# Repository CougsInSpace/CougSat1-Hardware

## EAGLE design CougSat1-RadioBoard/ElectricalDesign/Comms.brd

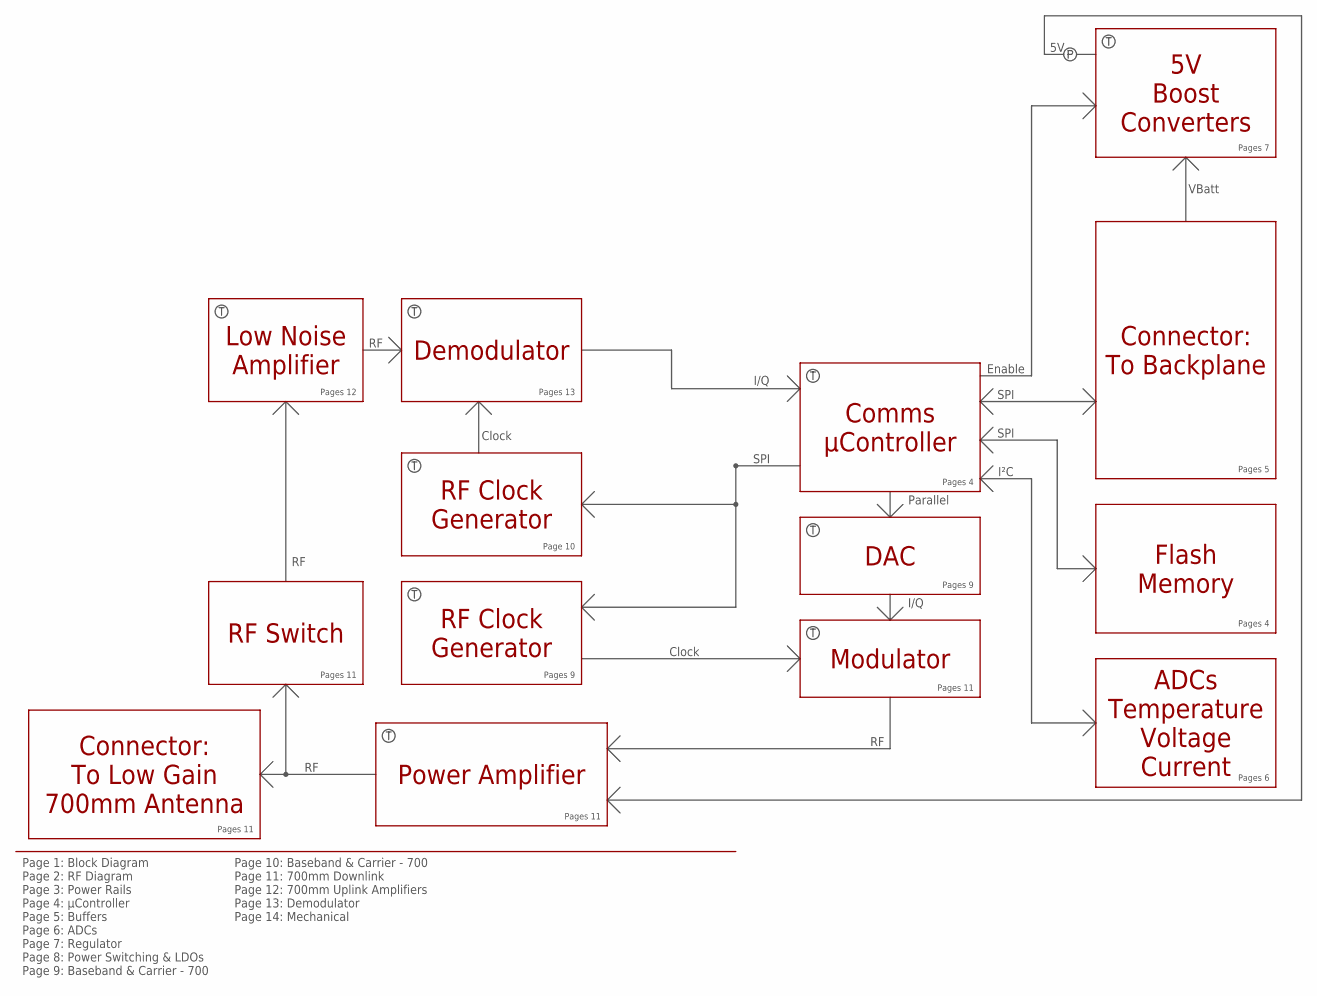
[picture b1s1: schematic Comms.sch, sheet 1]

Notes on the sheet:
Page 1: Block Diagram Page 2: RF Diagram Page 3: Power Rails Page 4: µController Page 5: Buffers Page 6: ADCs Page 7: Regulator Page 8: Power Switching & LDOs Page 9: Baseband & Carrier - 700
Connector: To Backplane
Comms µController
5V Boost Converters
Modulator
RF Clock Generator
Power Amplifier
Connector: To Low Gain 700mm Antenna
RF Switch
Demodulator
Low Noise Amplifier
ADCs Temperature Voltage Current
Flash Memory
VBatt
SPI
I/Q
Clock
Enable
I²C
Page 10: Baseband & Carrier - 700 Page 11: 700mm Downlink Page 12: 700mm Uplink Amplifiers Page 13: Demodulator Page 14: Mechanical
Pages 6
Page 10
DAC
Parallel
Pages 4
Pages 5
Pages 7
Pages 13
Pages 12
Pages 9
Pages 11

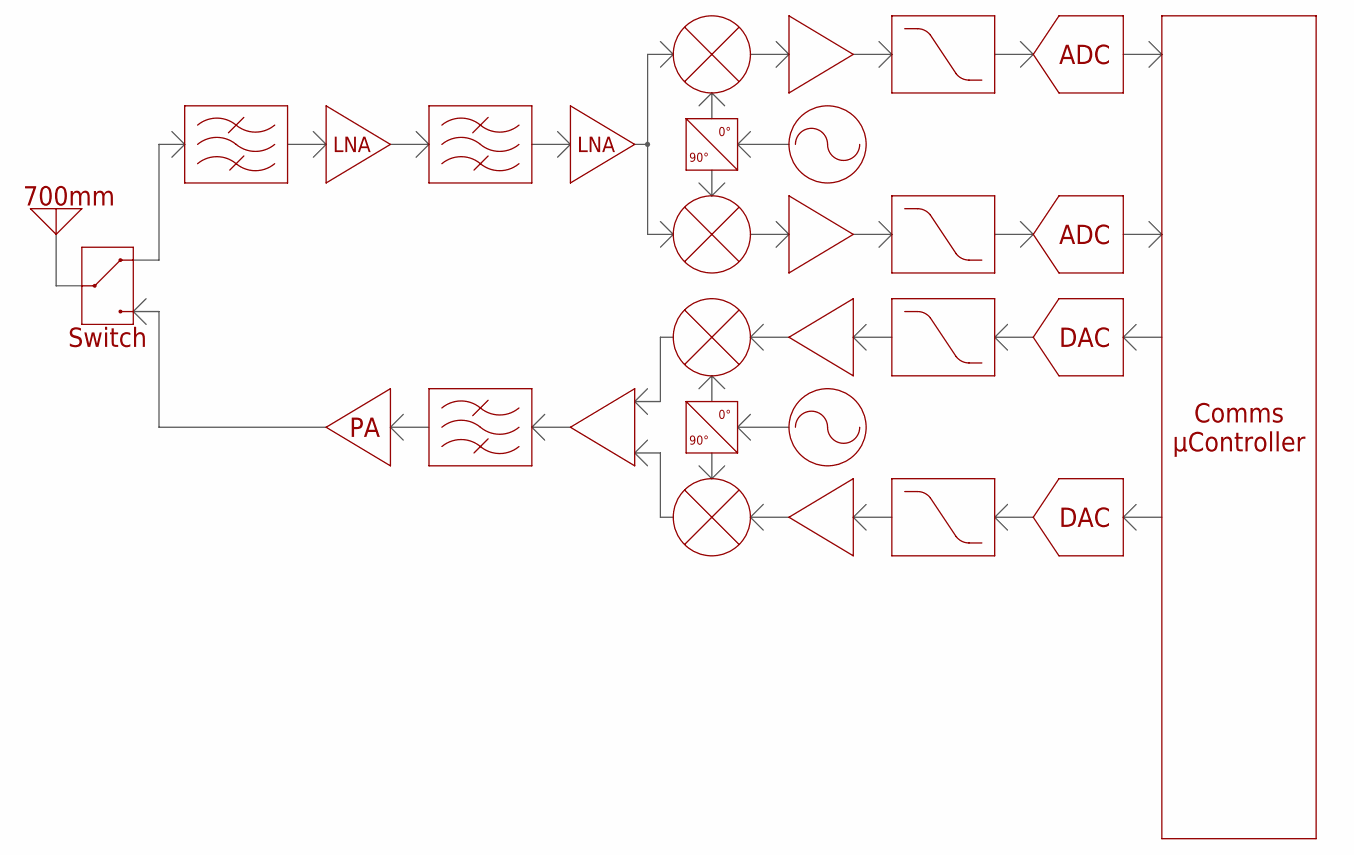
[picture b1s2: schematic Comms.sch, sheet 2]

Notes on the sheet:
LNA
DAC
ADC
90°
Switch
Comms µController
700mm

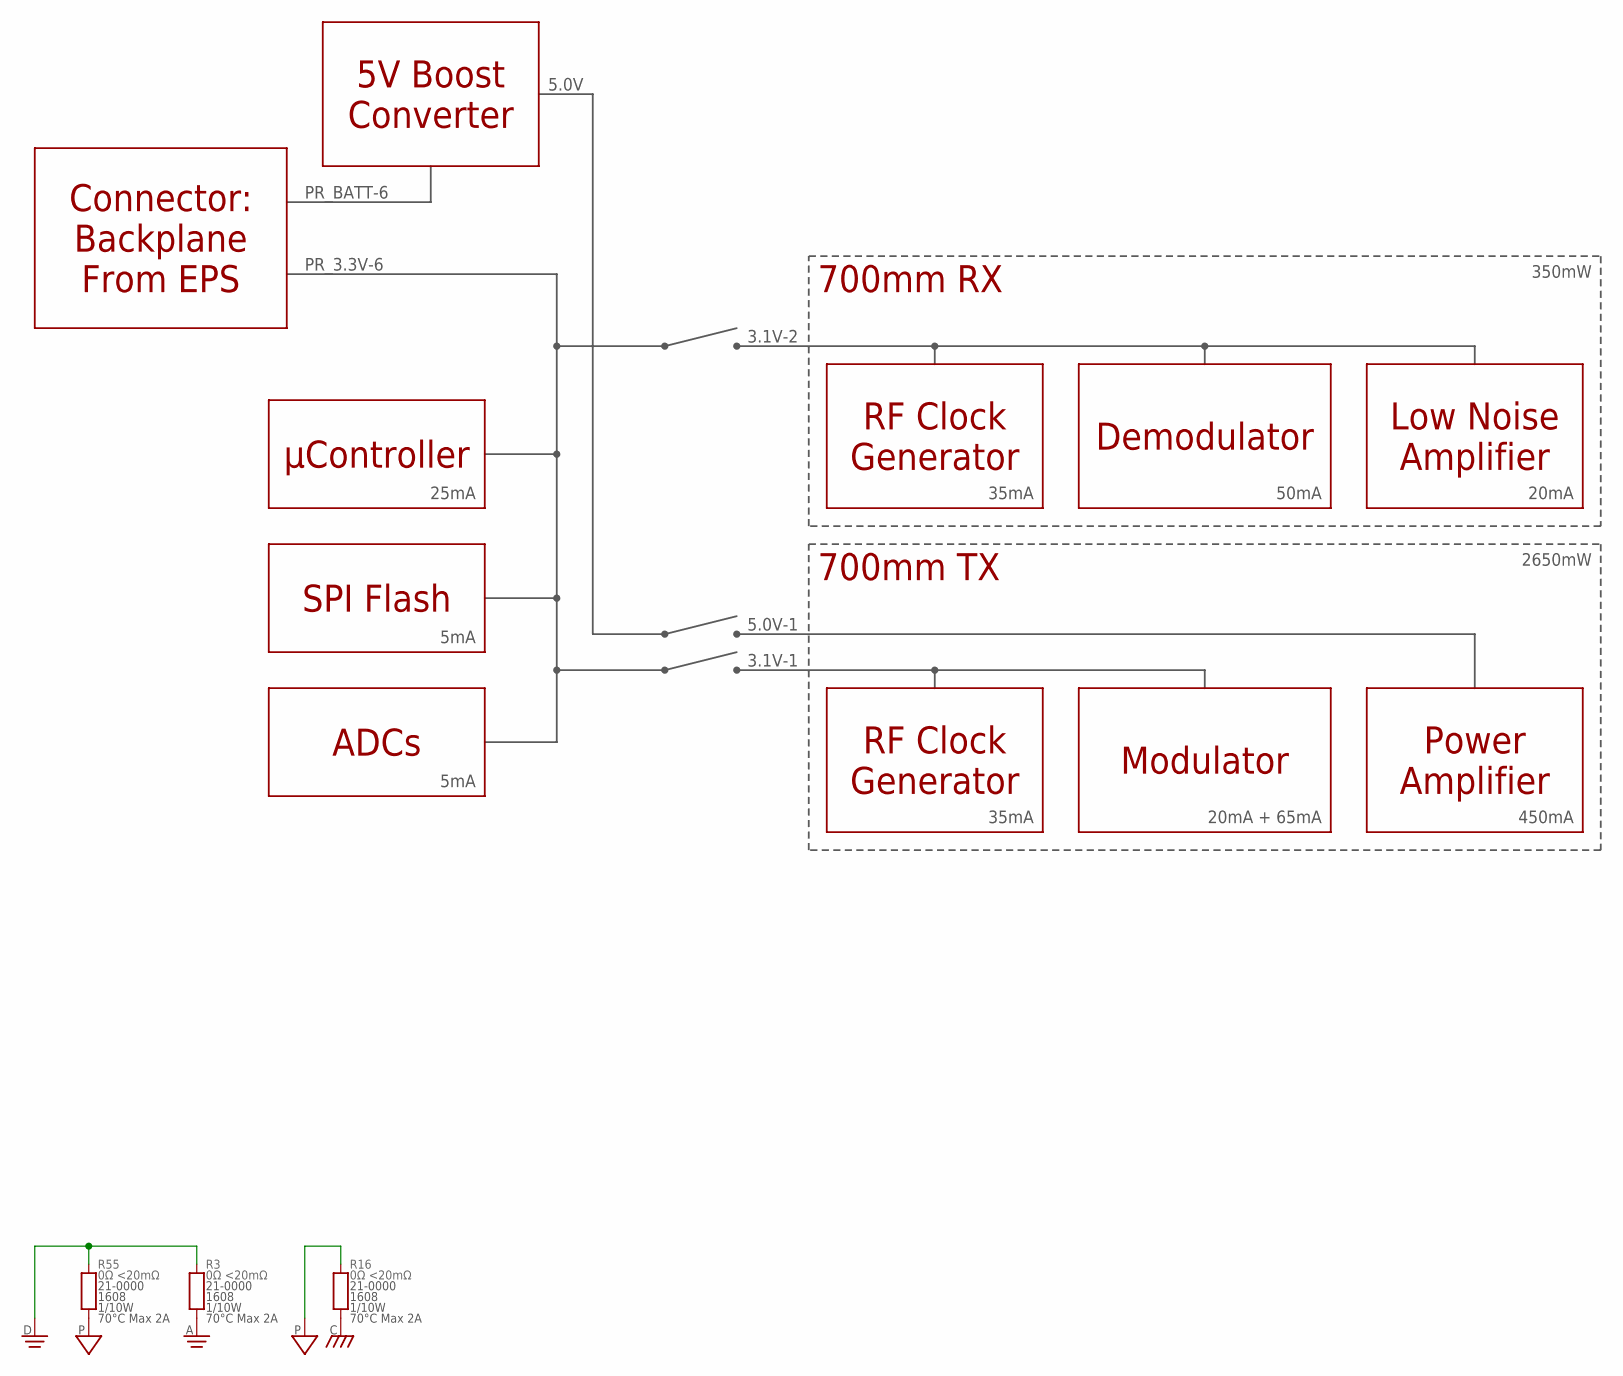
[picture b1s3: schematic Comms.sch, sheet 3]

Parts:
R3, R16, R55: 0Ω <20mΩ; 1608

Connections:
AGND: R3.1; also elsewhere on the board
CHASSIS: R16.1; also elsewhere on the board
DGND: R3.2, R55.2; also elsewhere on the board
PGND: R16.2, R55.1; also elsewhere on the board

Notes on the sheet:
Connector: Backplane From EPS
5V Boost Converter
µController
RF Clock Generator
Low Noise Amplifier
SPI Flash
ADCs
Demodulator
5.0V
PR_BATT-6
Modulator
700mm RX
700mm TX
3.1V-2
3.1V-1
PR_3.3V-6
5.0V-1
Power Amplifier
20mA
20mA + 65mA
50mA
35mA
450mA
25mA
5mA
350mW
2650mW

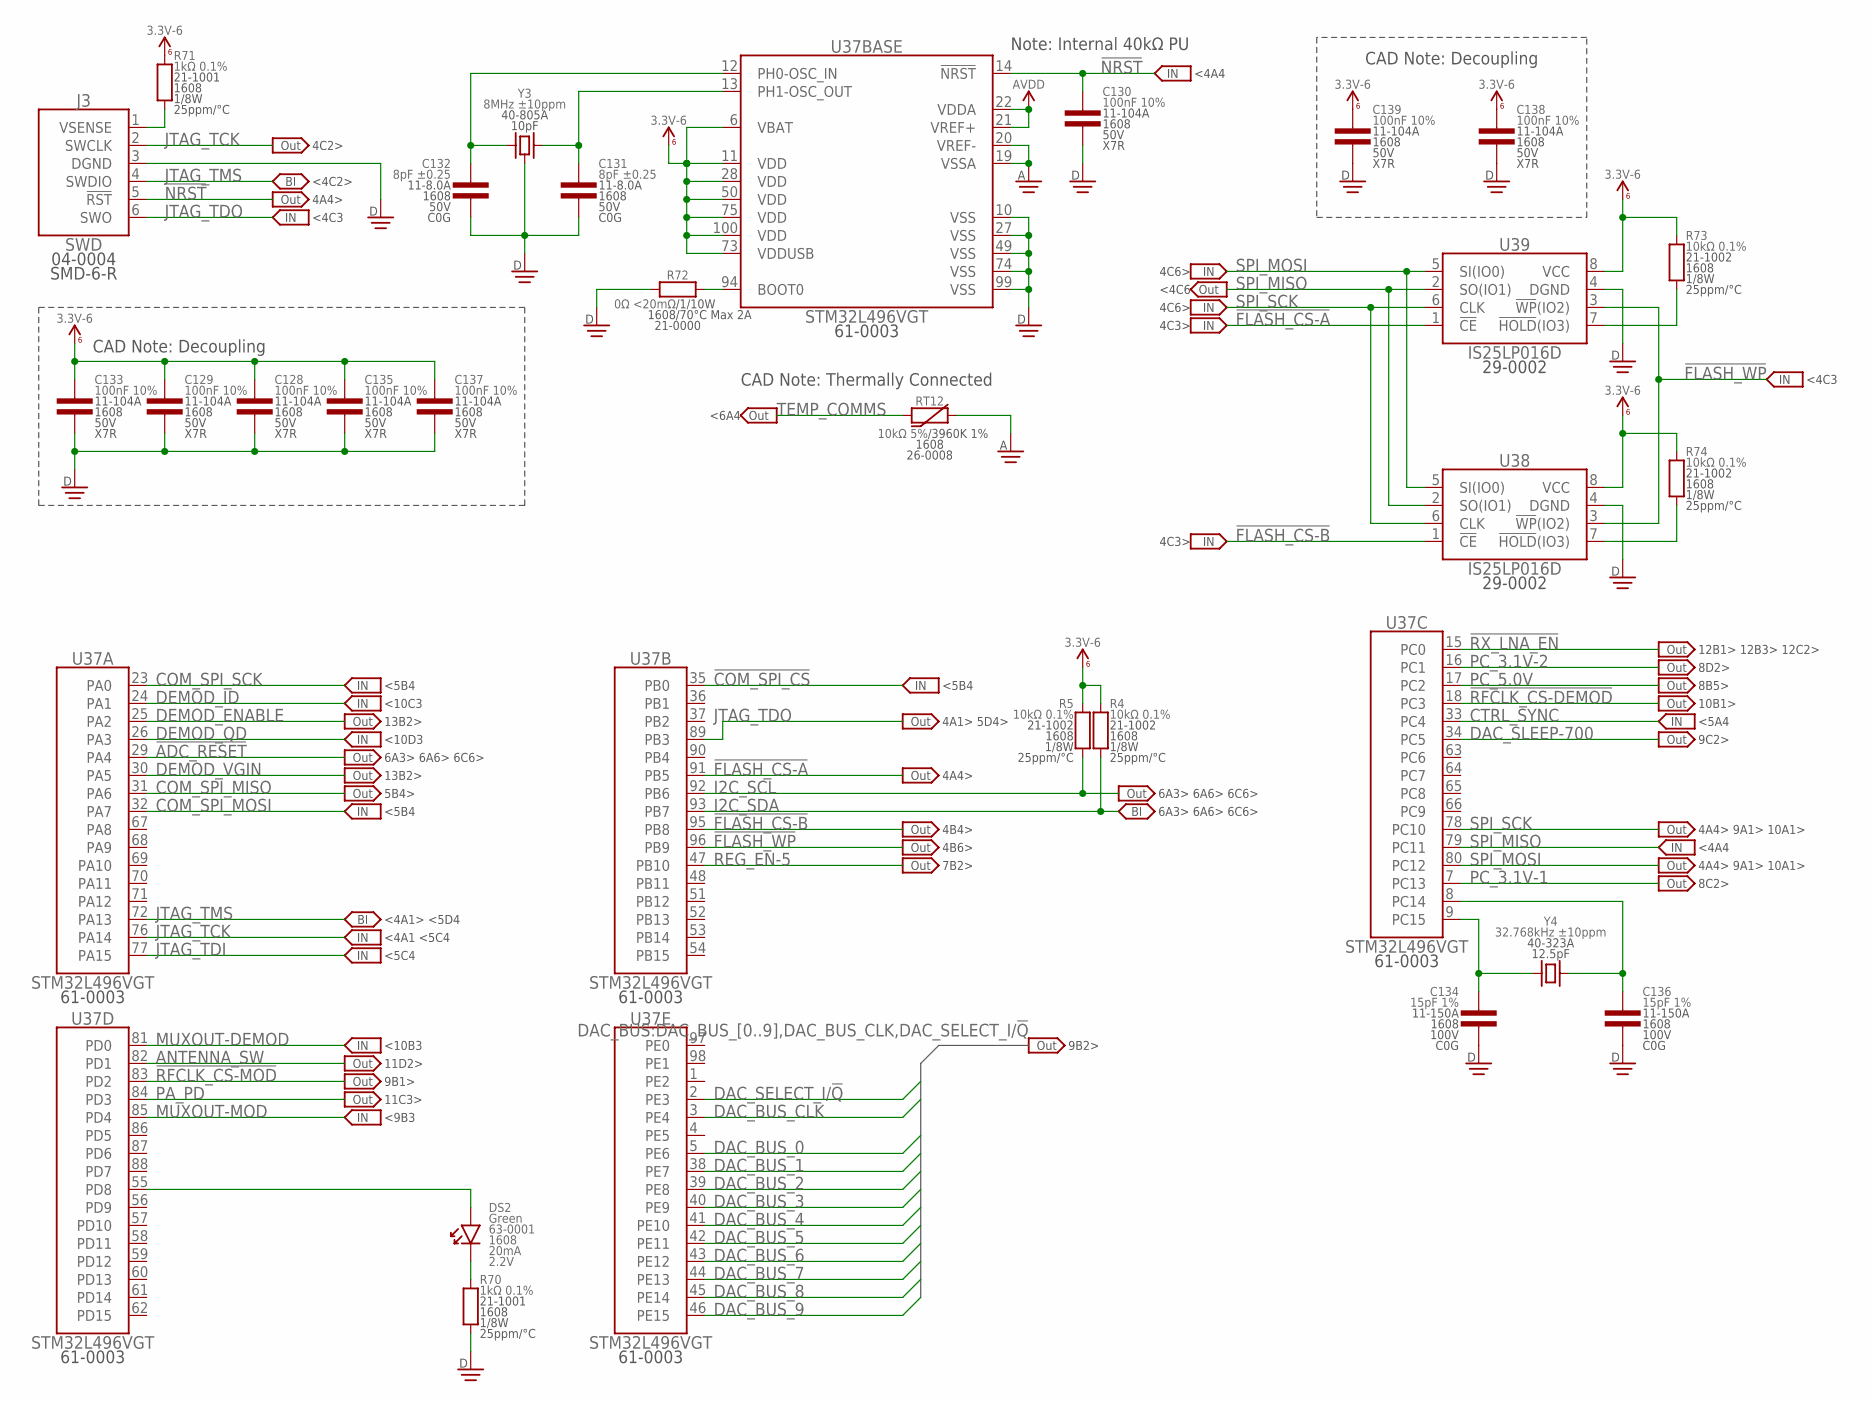
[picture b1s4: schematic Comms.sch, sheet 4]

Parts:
C128, C129, C130, C133, C135, C137, C138, C139: 100nF 10%; 1608
C131, C132: 8pF ±0.25; 1608
C134, C136: 15pF 1%; 1608
DS2: Green; 1608-POL
J3: SWD; SMD2.54-1X06-R
R4, R5, R73, R74: 10kΩ 0.1%; 1608
R70, R71: 1kΩ 0.1%; 1608
R72: 0Ω <20mΩ; 1608
RT12: 10kΩ 5%; 1608
U37: STM32L496VGT; QFP-100-1414
U38, U39: IS25LP016D; SO8
Y3: 8MHz ±10ppm; SMD-5032
Y4: 32.768kHz ±10ppm; SMD-3215

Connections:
3.3V_6: C128.1, C129.1, C133.1, C135.1, C137.1, C138.1, C139.1, R4.2, R5.2, R71.2, R73.2, R74.2, U37.6 (VBAT), U37.11 (VDD), U37.28 (VDD), U37.50 (VDD), U37.73 (VDDUSB), U37.75 (VDD), U37.100 (VDD), U38.8 (VCC), U39.8 (VCC); also elsewhere on the board
!ADC_RESET: U37.29 (PA4); also elsewhere on the board
!COM_SPI_CS: U37.35 (PB0); also elsewhere on the board
!FLASH_CS-A: U37.91 (PB5), U39.1 (!CE)
!FLASH_CS-B: U37.95 (PB8), U38.1 (!CE)
!FLASH_WP: U37.96 (PB9), U38.3 (!WP!(IO2)), U39.3 (!WP!(IO2))
!NRST: C130.1, J3.5 (!RST), U37.14 (!NRST)
!RFCLK_CS-DEMOD: U37.18 (PC3); also elsewhere on the board
!RFCLK_CS-MOD: U37.83 (PD2); also elsewhere on the board
!RX_LNA_EN: U37.15 (PC0); also elsewhere on the board
AGND: RT12.2, U37.19 (VSSA), U37.20 (VREF-); also elsewhere on the board
ANTENNA_SW: U37.82 (PD1); also elsewhere on the board
AVDD: U37.21 (VREF+), U37.22 (VDDA); also elsewhere on the board
BOOT0: R72.2, U37.94 (BOOT0)
COM_SPI_MISO: U37.31 (PA6); also elsewhere on the board
COM_SPI_MOSI: U37.32 (PA7); also elsewhere on the board
COM_SPI_SCK: U37.23 (PA0); also elsewhere on the board
CTRL_SYNC: U37.33 (PC4); also elsewhere on the board
DAC_BUS_0: U37.5 (PE6); also elsewhere on the board
DAC_BUS_1: U37.38 (PE7); also elsewhere on the board
DAC_BUS_2: U37.39 (PE8); also elsewhere on the board
DAC_BUS_3: U37.40 (PE9); also elsewhere on the board
DAC_BUS_4: U37.41 (PE10); also elsewhere on the board
DAC_BUS_5: U37.42 (PE11); also elsewhere on the board
DAC_BUS_6: U37.43 (PE12); also elsewhere on the board
DAC_BUS_7: U37.44 (PE13); also elsewhere on the board
DAC_BUS_8: U37.45 (PE14); also elsewhere on the board
DAC_BUS_9: U37.46 (PE15); also elsewhere on the board
DAC_BUS_CLK: U37.3 (PE4); also elsewhere on the board
DAC_SELECT_I/!Q: U37.2 (PE3); also elsewhere on the board
DAC_SLEEP-700: U37.34 (PC5); also elsewhere on the board
DEMOD_ENABLE: U37.25 (PA2); also elsewhere on the board
DEMOD_ID: U37.24 (PA1); also elsewhere on the board
DEMOD_QD: U37.26 (PA3); also elsewhere on the board
DEMOD_VGIN: U37.30 (PA5); also elsewhere on the board
DGND: C128.2, C129.2, C130.2, C131.2, C132.2, C133.2, C134.2, C135.2, C136.2, C137.2, C138.2, C139.2, J3.3 (DGND), R70.1, R72.1, U37.10 (VSS), U37.27 (VSS), U37.49 (VSS), U37.74 (VSS), U37.99 (VSS), U38.4 (DGND), U39.4 (DGND), Y3.2 (GND), Y3.4 (GND); also elsewhere on the board
FLASH_HOLD-A: R73.1, U39.7 (!HOLD!(IO3))
FLASH_HOLD-B: R74.1, U38.7 (!HOLD!(IO3))
I2C_SCL: R5.1, U37.92 (PB6); also elsewhere on the board
I2C_SDA: R4.1, U37.93 (PB7); also elsewhere on the board
JTAG_TCK: J3.2 (SWCLK), U37.76 (PA14); also elsewhere on the board
JTAG_TDI: U37.77 (PA15); also elsewhere on the board
JTAG_TDO: J3.6 (SWO), U37.89 (PB3); also elsewhere on the board
JTAG_TMS: J3.4 (SWDIO), U37.72 (PA13); also elsewhere on the board
LED_A: DS2.A, U37.55 (PD8)
LED_C: DS2.C, R70.2
MUXOUT-DEMOD: U37.81 (PD0); also elsewhere on the board
MUXOUT-MOD: U37.85 (PD4); also elsewhere on the board
OSC32_IN: C136.1, U37.8 (PC14), Y4.2
OSC32_OUT: C134.1, U37.9 (PC15), Y4.1
OSC_IN: C132.1, U37.12 (PH0-OSC_IN), Y3.1
OSC_OUT: C131.1, U37.13 (PH1-OSC_OUT), Y3.3 (2)
PA_PD: U37.84 (PD3); also elsewhere on the board
PC_3.1V-1: U37.7 (PC13); also elsewhere on the board
PC_3.1V-2: U37.16 (PC1); also elsewhere on the board
PC_5.0V: U37.17 (PC2); also elsewhere on the board
REG_EN-5: U37.47 (PB10); also elsewhere on the board
SPI_MISO: U37.79 (PC11), U38.2 (SO(IO1)), U39.2 (SO(IO1))
SPI_MOSI: U37.80 (PC12), U38.5 (SI(IO0)), U39.5 (SI(IO0)); also elsewhere on the board
SPI_SCK: U37.78 (PC10), U38.6 (CLK), U39.6 (CLK); also elsewhere on the board
SWD_VSENSE: J3.1 (VSENSE), R71.1
TEMP_COMMS: RT12.1; also elsewhere on the board

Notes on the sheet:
CAD Note: Decoupling
Note: Internal 40kΩ PU
CAD Note: Thermally Connected
4C2>
<4C2>
<4C3
4A4>
<4A4
<4A1 <5C4
<4A1> <5D4
<5C4
4A1> 5D4>
<5B4
5B4>
<5A4
6A3> 6A6> 6C6>
4B4>
4B6>
4A4> 9A1> 10A1>
4C6>
<4C6
4C3>
<6A4
7B2>
8C2>
8B5>
8D2>
9B2>
<9B3
<10B3
9C2>
9B1>
10B1>
<10C3
<10D3
11D2>
11C3>
12B1> 12B3> 12C2>
13B2>

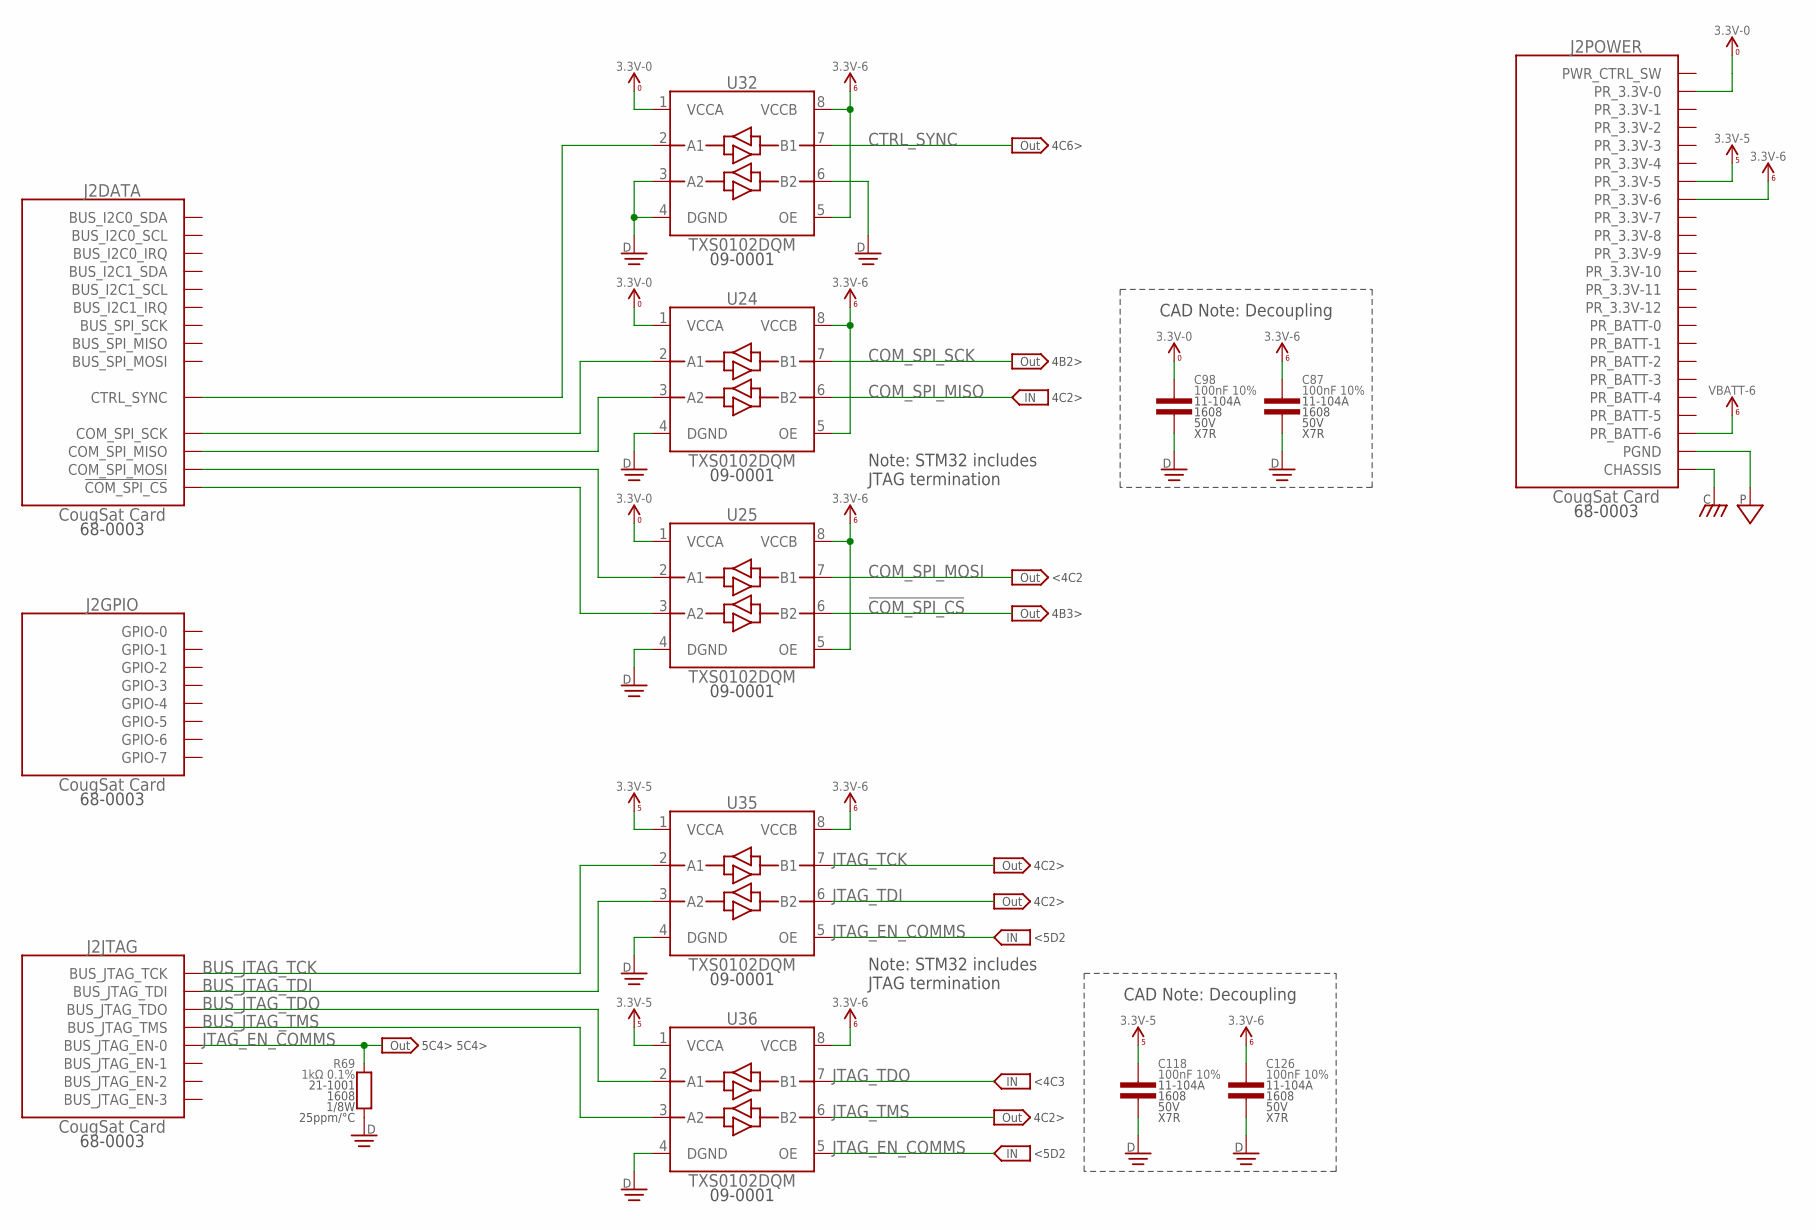
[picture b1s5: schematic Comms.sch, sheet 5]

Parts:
C87, C98, C118, C126: 100nF 10%; 1608
J2: CougSat Card; CARD-FULL-OPEN+X
R69: 1kΩ 0.1%; 1608
U24, U25, U32, U35, U36: TXS0102DQM; X2SON-8

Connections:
3.3V_0: C98.1, J2.A1 (PR_3.3V-0), J2.B1 (PR_3.3V-0), U24.1 (VCCA), U25.1 (VCCA), U32.1 (VCCA)
3.3V_5: C118.1, J2.A6 (PR_3.3V-5), J2.B6 (PR_3.3V-5), U35.1 (VCCA), U36.1 (VCCA)
3.3V_6: C87.1, C126.1, J2.A7 (PR_3.3V-6), J2.B7 (PR_3.3V-6), U24.5 (OE), U24.8 (VCCB), U25.5 (OE), U25.8 (VCCB), U32.5 (OE), U32.8 (VCCB), U35.8 (VCCB), U36.8 (VCCB); also elsewhere on the board
!BUS_COM_SPI_CS: J2.A36 (!COM_SPI_CS), J2.B36 (!COM_SPI_CS), U25.3 (A2)
!COM_SPI_CS: U25.6 (B2); also elsewhere on the board
BUS_COM_SPI_MISO: J2.A34 (COM_SPI_MISO), J2.B34 (COM_SPI_MISO), U24.3 (A2)
BUS_COM_SPI_MOSI: J2.A35 (COM_SPI_MOSI), J2.B35 (COM_SPI_MOSI), U25.2 (A1)
BUS_COM_SPI_SCK: J2.A33 (COM_SPI_SCK), J2.B33 (COM_SPI_SCK), U24.2 (A1)
BUS_CTRL_SYNC: J2.A42 (CTRL_SYNC), J2.B42 (CTRL_SYNC), U32.2 (A1)
BUS_JTAG_TCK: J2.A46 (BUS_JTAG_TCK), U35.2 (A1)
BUS_JTAG_TDI: J2.A47 (BUS_JTAG_TDI), U35.3 (A2)
BUS_JTAG_TDO: J2.A48 (BUS_JTAG_TDO), U36.2 (A1)
BUS_JTAG_TMS: J2.A49 (BUS_JTAG_TMS), U36.3 (A2)
CHASSIS: J2.CHASSIS@1 (CHASSIS), J2.CHASSIS@2 (CHASSIS), J2.CHASSIS@3 (CHASSIS), J2.CHASSIS@4 (CHASSIS); also elsewhere on the board
COM_SPI_MISO: U24.6 (B2); also elsewhere on the board
COM_SPI_MOSI: U25.7 (B1); also elsewhere on the board
COM_SPI_SCK: U24.7 (B1); also elsewhere on the board
CTRL_SYNC: U32.7 (B1); also elsewhere on the board
DGND: C87.2, C98.2, C118.2, C126.2, R69.1, U24.4 (DGND), U25.4 (DGND), U32.3 (A2), U32.4 (DGND), U32.6 (B2), U35.4 (DGND), U36.4 (DGND); also elsewhere on the board
JTAG_EN_COMMS: J2.B46 (BUS_JTAG_EN-0), R69.2, U35.5 (OE), U36.5 (OE)
JTAG_TCK: U35.7 (B1); also elsewhere on the board
JTAG_TDI: U35.6 (B2); also elsewhere on the board
JTAG_TDO: U36.7 (B1); also elsewhere on the board
JTAG_TMS: U36.6 (B2); also elsewhere on the board
PGND: J2.A21 (PGND), J2.A22 (PGND), J2.A23 (PGND), J2.B21 (PGND), J2.B22 (PGND), J2.B23 (PGND), J2.B24 (PGND), J2.B25 (PGND), J2.B26 (PGND), J2.B27 (PGND), J2.B28 (PGND), J2.B29 (PGND); also elsewhere on the board
PR_3.3V-1: J2.A2 (PR_3.3V-1), J2.B2 (PR_3.3V-1)
PR_3.3V-2: J2.A3 (PR_3.3V-2), J2.B3 (PR_3.3V-2)
PR_3.3V-3: J2.A4 (PR_3.3V-3), J2.B4 (PR_3.3V-3)
PR_3.3V-4: J2.A5 (PR_3.3V-4), J2.B5 (PR_3.3V-4)
PR_3.3V-7: J2.A8 (PR_3.3V-7), J2.B8 (PR_3.3V-7)
PR_3.3V-8: J2.A9 (PR_3.3V-8), J2.B9 (PR_3.3V-8)
PR_3.3V-9: J2.A10 (PR_3.3V-9), J2.B10 (PR_3.3V-9)
PR_3.3V-10: J2.A11 (PR_3.3V-10), J2.B11 (PR_3.3V-10)
PR_3.3V-11: J2.A12 (PR_3.3V-11), J2.B12 (PR_3.3V-11)
PR_3.3V-12: J2.A13 (PR_3.3V-12), J2.B13 (PR_3.3V-12)
PR_BATT-0: J2.A14 (PR_BATT-0), J2.B14 (PR_BATT-0)
PR_BATT-1: J2.A15 (PR_BATT-1), J2.B15 (PR_BATT-1)
PR_BATT-2: J2.A16 (PR_BATT-2), J2.B16 (PR_BATT-2)
PR_BATT-3: J2.A17 (PR_BATT-3), J2.B17 (PR_BATT-3)
PR_BATT-4: J2.A18 (PR_BATT-4), J2.B18 (PR_BATT-4)
PR_BATT-5: J2.A19 (PR_BATT-5), J2.B19 (PR_BATT-5)
VBATT_6: J2.A20 (PR_BATT-6), J2.B20 (PR_BATT-6); also elsewhere on the board

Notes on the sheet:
<5D2
CAD Note: Decoupling
4C2>
Note: STM32 includes JTAG termination
<4C3
5C4> 5C4>
4B2>
4B3>
<4C2
4C6>

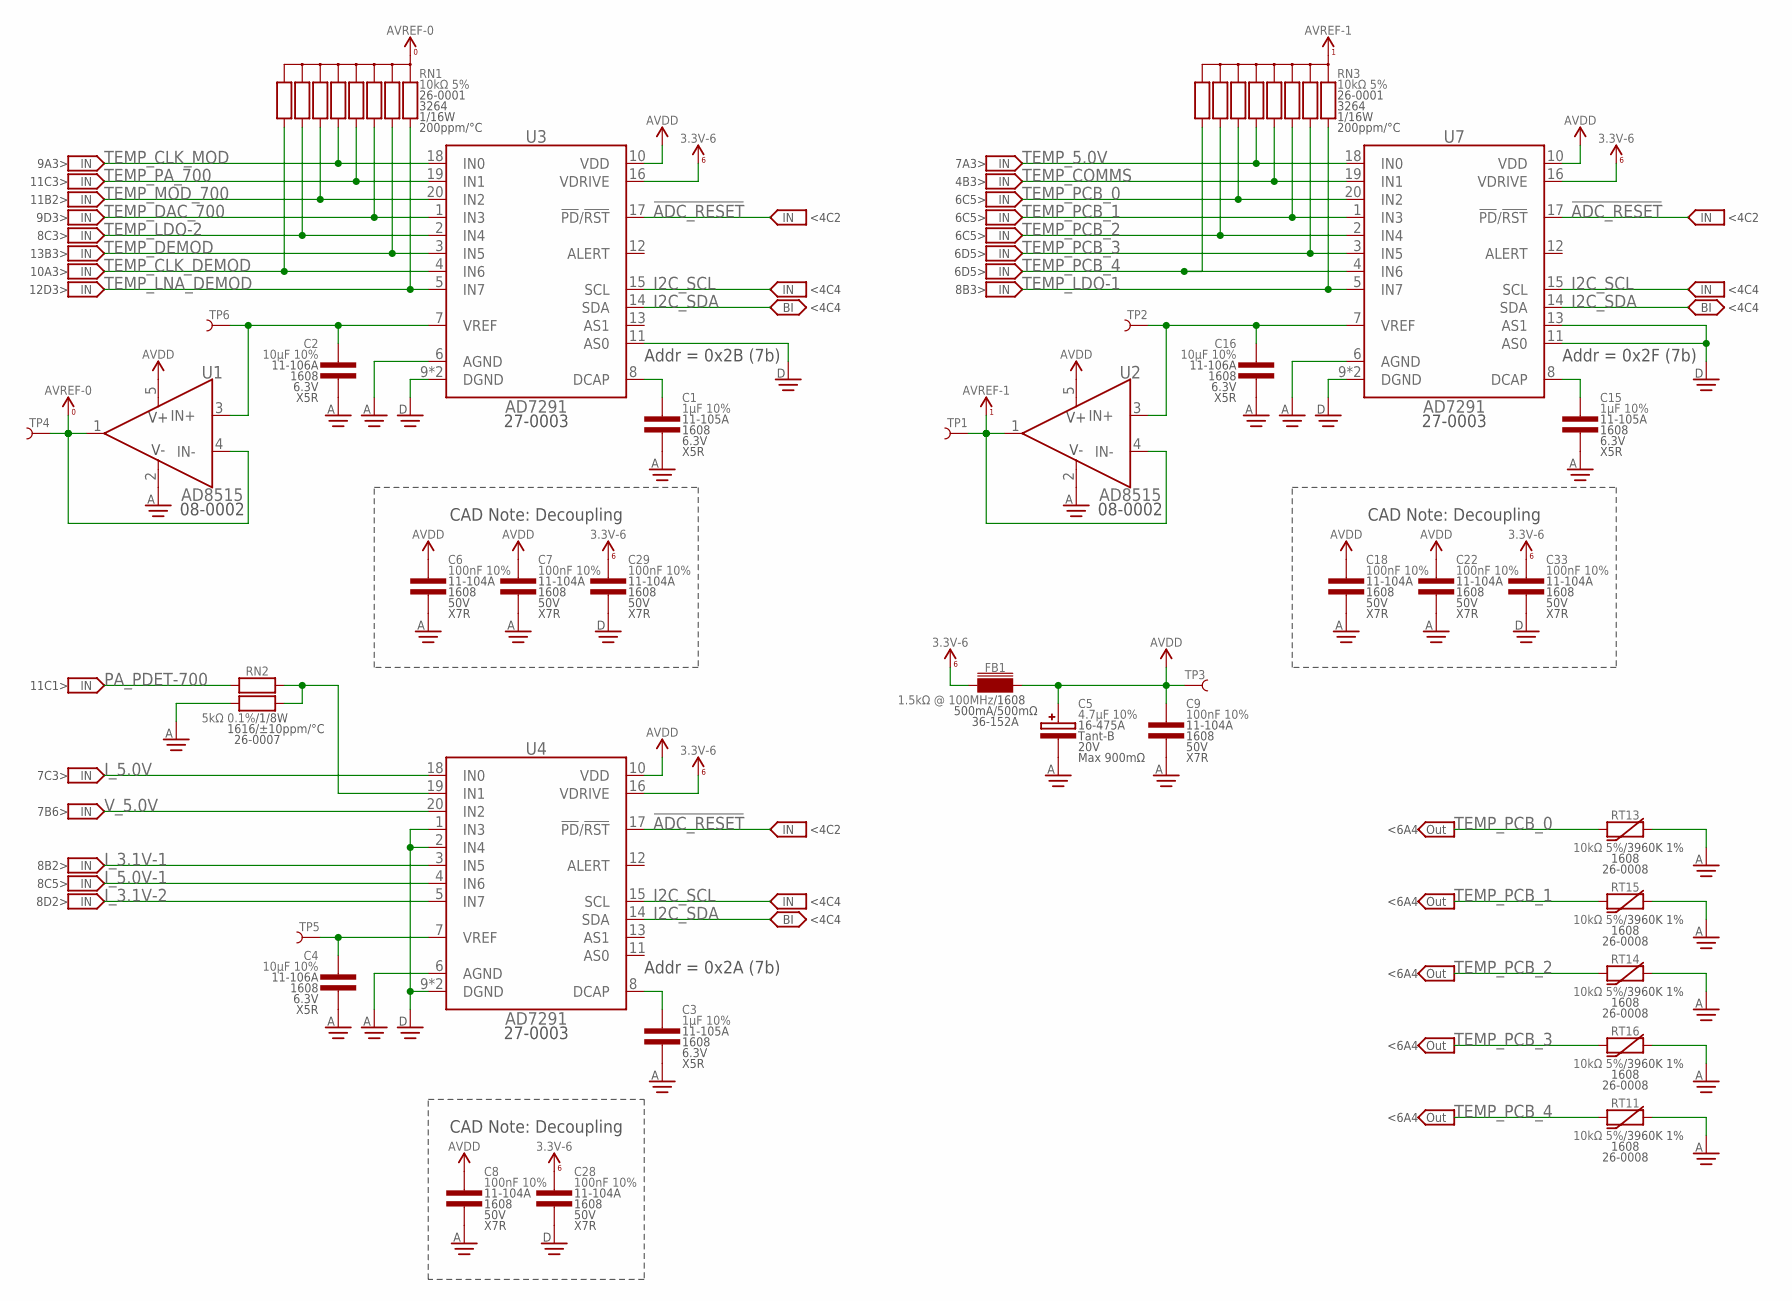
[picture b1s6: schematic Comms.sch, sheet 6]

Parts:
C1, C3, C15: 1µF 10%; 1608
C2, C4, C16: 10µF 10%; 1608
C5: 4.7µF 10%; 4028-POL
C6, C7, C8, C9, C18, C22, C28, C29, C33: 100nF 10%; 1608
FB1: 1.5kΩ @ 100MHz; 1608
RN1, RN3: 10kΩ 5%; 3264
RN2: 5kΩ 0.1%; 1616
RT11, RT13, RT14, RT15, RT16: 10kΩ 5%; 1608
TP1, TP2, TP3, TP4, TP5, TP6: TEST_POINT-SMD-C-1.25; SMD-C-1.25
U1, U2: AD8515; SOT23-5
U3, U4, U7: AD7291; QFN-20-4040

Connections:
3.3V_6: C28.1, C29.1, C33.1, FB1.1, U3.16 (VDRIVE), U4.16 (VDRIVE), U7.16 (VDRIVE); also elsewhere on the board
!ADC_RESET: U3.17 (!PD!/!RST), U4.17 (!PD!/!RST), U7.17 (!PD!/!RST); also elsewhere on the board
ADC_DCAP-0: C1.1, U3.8 (DCAP)
ADC_DCAP-1: C15.1, U7.8 (DCAP)
ADC_DCAP-2: C3.1, U4.8 (DCAP)
ADC_PA_PDET-700: RN2.3 (B2), RN2.4 (A2), U4.19 (IN1)
ADC_VREF-0: C2.1, TP6.1, U1.3 (IN+), U3.7 (VREF)
ADC_VREF-1: C16.1, TP2.1, U2.3 (IN+), U7.7 (VREF)
ADC_VREF-2: C4.1, TP5.1, U4.7 (VREF)
AGND: C1.2, C2.2, C3.2, C4.2, C5.C, C6.2, C7.2, C8.2, C9.2, C15.2, C16.2, C18.2, C22.2, RN2.1 (A1), RT11.2, RT13.2, RT14.2, RT15.2, RT16.2, U1.2 (V-), U2.2 (V-), U3.6 (AGND), U4.6 (AGND), U7.6 (AGND); also elsewhere on the board
AVDD: C5.A, C6.1, C7.1, C8.1, C9.1, C18.1, C22.1, FB1.2, TP3.1, U1.5 (V+), U2.5 (V+), U3.10 (VDD), U4.10 (VDD), U7.10 (VDD); also elsewhere on the board
AVREF-0: RN1.5 (C), RN1.10 (C), TP4.1, U1.1 (OUT), U1.4 (IN-)
AVREF-1: RN3.5 (C), RN3.10 (C), TP1.1, U2.1 (OUT), U2.4 (IN-)
DGND: C28.2, C29.2, C33.2, U3.9 (DGND), U3.11 (AS0), U3.PAD (DGND), U4.1 (IN3), U4.2 (IN4), U4.9 (DGND), U4.PAD (DGND), U7.9 (DGND), U7.11 (AS0), U7.13 (AS1), U7.PAD (DGND); also elsewhere on the board
I2C_SCL: U3.15 (SCL), U4.15 (SCL), U7.15 (SCL); also elsewhere on the board
I2C_SDA: U3.14 (SDA), U4.14 (SDA), U7.14 (SDA); also elsewhere on the board
I_3.1V-1: U4.3 (IN5); also elsewhere on the board
I_3.1V-2: U4.5 (IN7); also elsewhere on the board
I_5.0V: U4.18 (IN0); also elsewhere on the board
I_5.0V-1: U4.4 (IN6); also elsewhere on the board
PA_PDET-700: RN2.2 (B1); also elsewhere on the board
TEMP_5.0V: RN3.6 (5), U7.18 (IN0); also elsewhere on the board
TEMP_CLK_DEMOD: RN1.9 (8), U3.4 (IN6); also elsewhere on the board
TEMP_CLK_MOD: RN1.6 (5), U3.18 (IN0); also elsewhere on the board
TEMP_COMMS: RN3.4, U7.19 (IN1); also elsewhere on the board
TEMP_DAC_700: RN1.3, U3.1 (IN3); also elsewhere on the board
TEMP_DEMOD: RN1.2, U3.3 (IN5); also elsewhere on the board
TEMP_LDO-1: RN3.1, U7.5 (IN7); also elsewhere on the board
TEMP_LDO-2: RN1.8 (7), U3.2 (IN4); also elsewhere on the board
TEMP_LNA_DEMOD: RN1.1, U3.5 (IN7); also elsewhere on the board
TEMP_MOD_700: RN1.7 (6), U3.20 (IN2); also elsewhere on the board
TEMP_PA_700: RN1.4, U3.19 (IN1); also elsewhere on the board
TEMP_PCB_0: RN3.7 (6), RT13.1, U7.20 (IN2)
TEMP_PCB_1: RN3.3, RT15.1, U7.1 (IN3)
TEMP_PCB_2: RN3.8 (7), RT14.1, U7.2 (IN4)
TEMP_PCB_3: RN3.2, RT16.1, U7.3 (IN5)
TEMP_PCB_4: RN3.9 (8), RT11.1, U7.4 (IN6)
V_5.0V: U4.20 (IN2); also elsewhere on the board

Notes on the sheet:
<4C2
<4C4
CAD Note: Decoupling
Addr = 0x2B (7b)
Addr = 0x2F (7b)
Addr = 0x2A (7b)
4B3>
7A3>
8B3>
8C3>
8B2>
8D2>
8C5>
7C3>
7B6>
6C5>
9A3>
9D3>
10A3>
11B2>
11C3>
12D3>
13B3>
11C1>
<6A4
6D5>

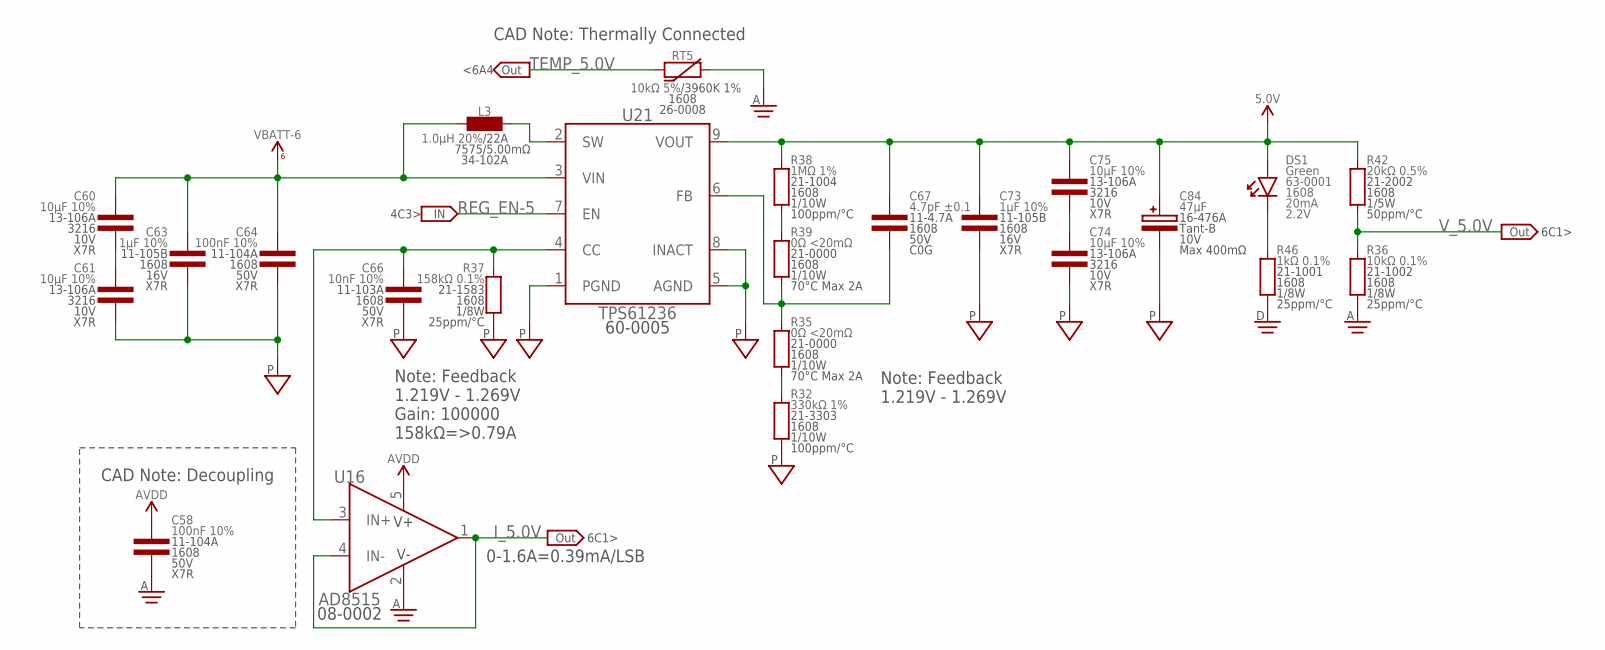
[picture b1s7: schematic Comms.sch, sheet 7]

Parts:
C58, C64: 100nF 10%; 1608
C60, C61, C74, C75: 10µF 10%; 3216
C63, C73: 1µF 10%; 1608
C66: 10nF 10%; 1608
C67: 4.7pF ±0.1; 1608
C84: 47µF; 4028-POL
DS1: Green; 1608-POL
L3: 1.0µH 20%; 7575
R32: 330kΩ 1%; 1608
R35, R39: 0Ω <20mΩ; 1608
R36: 10kΩ 0.1%; 1608
R37: 158kΩ 0.1%; 1608
R38: 1MΩ 1%; 1608
R42: 20kΩ 0.5%; 1608
R46: 1kΩ 0.1%; 1608
RT5: 10kΩ 5%; 1608
U16: AD8515; SOT23-5
U21: TPS61236; QFN-TPS6123X

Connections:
5.0V: C67.1, C73.1, C75.1, C84.A, DS1.A, R38.2, R42.2, U21.9 (VOUT); also elsewhere on the board
AGND: C58.2, R36.1, RT5.2, U16.2 (V-); also elsewhere on the board
AVDD: C58.1, U16.5 (V+); also elsewhere on the board
DGND: R46.1; also elsewhere on the board
I_5.0V: U16.1 (OUT), U16.4 (IN-); also elsewhere on the board
LED_C-5: DS1.C, R46.2
PGND: C61.2, C63.2, C64.2, C66.2, C73.2, C74.2, C84.C, R32.1, R37.1, U21.1 (PGND), U21.5 (AGND), U21.8 (INACT); also elsewhere on the board
REG_CC-5: C66.1, R37.2, U16.3 (IN+), U21.4 (CC)
REG_CIN-5: C60.2, C61.1
REG_COUT-5: C74.1, C75.2
REG_EN-5: U21.7 (EN); also elsewhere on the board
REG_FB-5: C67.2, R35.2, R39.1, U21.6 (FB)
REG_FB_RES-HIGH-5: R38.1, R39.2
REG_FB_RES-LOW-5: R32.2, R35.1
REG_SW-5: L3.2, U21.2 (SW)
TEMP_5.0V: RT5.1; also elsewhere on the board
VBATT_6: C60.1, C63.1, C64.1, L3.1, U21.3 (VIN); also elsewhere on the board
V_5.0V: R36.2, R42.1; also elsewhere on the board

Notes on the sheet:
Note: Feedback 1.219V - 1.269V
Note: Feedback 1.219V - 1.269V Gain: 100000 158kΩ=>0.79A
CAD Note: Thermally Connected
0-1.6A=0.39mA/LSB
CAD Note: Decoupling
<6A4
6C1>
4C3>
